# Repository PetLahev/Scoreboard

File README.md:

# Scoreboard 
Scoreboard created with [LED strips](https://www.amazon.com/FAVOLCANO-Waterproof-Feet%EF%BC%885M%EF%BC%89-Flexible-Lighting/dp/B012FFZP70/ref=sr_1_28_sspa?keywords=LED+Strips+red&qid=1554275786&s=gateway&sr=8-28-spons&psc=1), ~~[Arduino Nano](https://www.amazon.com/Arduino-A000005-ARDUINO-Nano/dp/B0097AU5OU/ref=sr_1_15?keywords=Arduino+Nano&qid=1554232867&s=gateway&sr=8-15)~~ [Arduino Uno](https://www.amazon.com/Arduino-A000066-ARDUINO-UNO-R3/dp/B008GRTSV6/ref=sr_1_3?keywords=arduino+UNO&qid=1555441457&s=gateway&sr=8-3) and some manual work. Handy for volleyball, table tennis, badminton, football etc.

### Why Arduino UNO
I wanted to use Nano and I designed the motherboard for using Nano but unfortunately it appeared to have one, not that serious problem for others,  but [blocker for me](https://stackoverflow.com/questions/55680065/arduino-nano-hm-10-module-not-receiving-data-on-mobile?noredirect=1#comment98070429_55680065). I was basically not able to send messages back to the HM-10 bluetooth module which is the 'main feature' of this whole scoreboard.
Thus after I built everything and was in the testing phase I found out that bluetooth communication is not working as I like. So instead of using the motherboard PCB I simply bought [UNO holder](https://store.arduino.cc/holder-type-uno) and a [terminal for UNO](https://www.amazon.com/Aideepen-Assembled-Prototype-Expansion-Bareboard/dp/B01JFQQXRS/ref=sr_1_3?keywords=arduino+UNO+terminal&qid=1555441354&s=gateway&sr=8-3) and made the scoreboard with it. Not that big problem as I have enough space in the box but hey ...

* 50 x 70 cm (19.7 x 27.55 inch) height x width
* Each segment 10 cm (3.93 inch) length so 20 cm (7.9 inch) one number! (*for points*)
* Each LED strip controlled by its own transistor
* Controlled by bluetooth module ([HM-10 Bluetooth 4.0 BLE](https://www.amazon.com/DSD-TECH-Bluetooth-iBeacon-Arduino/dp/B06WGZB2N4/ref=sr_1_1_sspa?keywords=HM-10-Bluetooth&qid=1554232302&s=gateway&sr=8-1-spons&psc=1))
    * Also possible to control via 433MHz module or an infra red (IR) controller
* You can use pre-defined setup for a game
* You can setup your own game
* Supports tiebreaks, sets and displaying players on service
* Score can be updated by buttons (either wired or wireless)
* As of April 2019 a free Androind application is used for controlling the scoreboard - [Serial Bluetooth Terminal](https://play.google.com/store/apps/details?id=de.kai_morich.serial_bluetooth_terminal&hl=en_US) v1.17
	* Update Feb 2021 - It was proven that the most convinient way how to control the scoreboard is an IR controller (people tend to prefer this way over others)
* Eagle schematic and boards included
* The scoreboard case designed on thinkercad.com
    * [The box](https://www.tinkercad.com/things/gNmK0jQ22qv)
    * [The display board](https://www.tinkercad.com/things/9Don7XhJEvx) - just for measuring purpose

## Setting the Serial Bluetooth Terminal
Just one device can be connected to the module at time!
Make sure you pair the bluetooth module with your smart phone, add it under the `Devices` tab and then go to the `Settings - Send` and set the `Newline` option to **none**. On the main menu tap on the connect symbol. You should get a text saying "Connected to unnamed". (*Make sure you bluetooth module is powered and the indication LED is blinking*)

## Settings
By default, the scoreboard is set as a clock (sets segment are used for seconds). There is no specific setting for turning the clock
off as this is always done by providing any setting. If you need to go back to the 'clock' mode, just turn the power off and then on.
You can setup your own game either in code - [globals.cpp](/Arduino/Scoreboard/src/globals.cpp) - or at runtime when sending the SETTING character via the Serial Bluetooth Terminal. The SETTING character is = `!` (*exclamation mark*). This behaves as a toggle switch so when send first time `!` the scoreboard will switch to 'setting mode' and will accept certain settings, when sending second time `!` it will end the 'setting mode' and will be ready for a game!

You can setup
* Number of sets (up to 9)
* Sets support - enabled/disabled
    * Number of points per a set (up to 99)
* Points difference to win a set
* Tiebreak support - enabled/disabled
    * Points in tiebreak
    * Points difference to win a tiebreak set
    * The tiebreak set
        * Set a number that represents the set in the match considered as tiebreak set. *For example, in tennis you would set number `7` here*
* Display player on service (*pre-set 4 players*) - enabled/disabled

### Application settings
The code now (*April 2019*) understands certain `key=value` pairs. Listed below but always check [settingController](/Arduino/Scoreboard/src/settingController.h) header file for the latest settings
* Enable displaying sets = `b`
* Sets per match = `s`
* Points per set = `e`
* Points difference to win a set = `d`
* Support tiebreak = `t`
* Set the tiebreak set = `q`
* Points in tiebreak = `f`
* Points difference to win a tiebreak = `w`
* Enable displaying a player on service = `r`
* Swap score = `$`
* Set player on service = `p` and then number 1 - 4
* Reset the whole game = `@`
* Turn sets segments to minute timer = `u`
    * Will automatically enable displaying sets

Examples of key-value setting

    b=true
    WIll enable sets (the LEDs will be powered)

    s=2
    A team/player needs to win 2 sets to win the match

    e=11
    A team/player needs to win 11 points to win a set
    (The points difference setting will be considered here)

    d=2
    A set will be considered as finished when the score between the teams/players
    1, reach the minimum points to win a set (e.g. 11)
    AND
    2, the difference is equal to 2
    examples: 11:9 or 13:11 or 12:10 or 21:19 etc.

    t=true
    Tiebreak is enabled

    q=2
    The tiebreak set is the second set to win. In other words this will be the third set
    For the above example the tiebreak settings will be considered when sets are 1:1

    f=9
    A team/player needs to win 9 points to win the tiebreak set

    w=2
    The tiebreak will be considered as finished when the score between the teams/players
    1, reach the minimum points to win the tiebreak set (e.g. 9)
    AND
    2, the difference is equal to 2
    examples: 9:7 or 10:8 or 11:9 etc.

    r=true
    Will enable displaying player on service (The LEDs will be powered)
    Note: There are always 4 players pre-set, not configurable as of April 2019)

    u=true
    Will turn the sets segments to display minute timer. So it will count from 0 to 9999 minutes

### Example of game settings
#### A free match (like football)
    b=false   ' disable sets
    s=0       ' no sets per match  
    e=99      ' set maximum of points
    t=false   ' tiebreak disabled
    r=false   ' disable displaying player on service

#### A beach volleyball match
    b=true    ' enable sets
    s=2       ' a team needs to win 2 sets to win a match
    e=21      ' a team needs to win 21 points to win a set
    d=2       ' the points difference between the two teams must be 2 to win a set
    t=reuw    ' tiebreak enabled
    q=2       ' the tiebreak set is the second one to win. So the sets score is 1:1
    f=15      ' a team needs to win 15 points to win the tiebreak set
    w=2       ' the points difference between the two teams must be 2 to win the tiebreak set
    r=true    ' enable displaying a player who serves

## How to use
Once your game is set and you leave the settings mode (*by sending `!` flag*) your match can start. Based on the type of your match the scoreboard will control all the aspect of the match you will just increase or decrease number of points for the **Home** or **Away** team

Send  
`h` - to give a point to **Home** team  
`a` - to give a point to **Away** team

If you make a mistake (*we all do*) you can take a point back.  
Send  
`v` - to decrease points of **Home** team  
`m` - to decrease score of **Away** team

**Please note:** Taking point back may have an affect on number of sets played, match finished, player on service etc. The code as of April 2019 cares just about simple cases and supports returning all back just for *one* point so if you made a mistake and give a point in the middle of set to a wrong team, taking the point back will work but if you made the same mistake when the team you gave won a set/match then taking the point back will NOT have any affect. It's better to start a new match by resetting the match and setting the correct score by sending few `h` or `a`.

## How to build
OK if you get here you actually may want to build your own scoreboard and I do understand that, it's much more fun!

If you just want to take the code and change it be aware that I didn't use the official Arduino IDE as I didn't find it as good as it should be. This project is made by [Visual Studio Code](https://code.visualstudio.com/) and [Platform IO](https://platformio.org/) extension both free. Once installed you should be able to build the project as it has all the settings done so you will get the right versions of used libraries and everything else. Please check [platformio.ini](/Arduino/platformio.ini) file to see if I added your Arduino board to the environment configuration. As of April 2019 I have this configuration

    [platformio]
    env_default = uno

    [env:nanoatmega328]
    platform = atmelavr
    board = nanoatmega328
    framework = arduino

    [env:uno]
    platform = atmelavr
    framework = arduino
    board = uno

The `env_default = uno` specifies for which board Platform IO builds the code, in this case is Arduino Uno. Make sure you have the right one here otherwise the code won't work.  
Let me also make you aware that I'm not C++ guy and I found it pretty hard to learn so the code is probably all messy but working.

If you also want to build the scoreboard case check the [Tinkercad page](https://www.tinkercad.com/things/gNmK0jQ22qv). I tried to make it in 1:5 scale but again it was my first experience with 3D software. The [shield](https://www.tinkercad.com/things/9Don7XhJEvx) is there only for measurement purpose. I just wanted to see to what size all the LED strips will fit and how it will look like. Based on the size I designed the [case](https://www.tinkercad.com/things/gNmK0jQ22qv).  
In terms of material use whatever will fit you. My original plan was using plastic because I didn't want to make it heavy but still not too fragile. For the first version I ended up with a 5mm wood board you can buy in hobby markets asked a joiner to cut the board into pieces and let him actually figure out how to put it all together, it cost me just ~$10 then you just need to a drill and couple screws and put it all together

To be continued

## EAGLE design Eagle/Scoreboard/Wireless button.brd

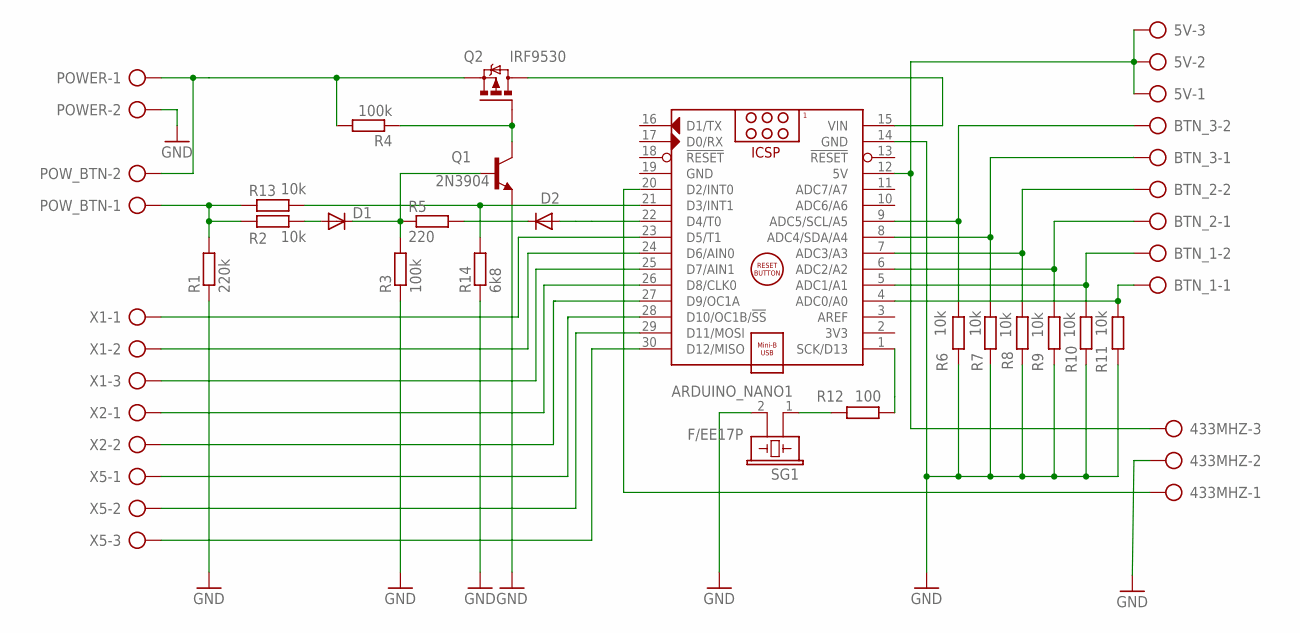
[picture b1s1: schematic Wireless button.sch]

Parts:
5V, 433MHZ: AK500/3
ARDUINO_NANO1: ARDUINO_NANO
BTN_1, BTN_2, BTN_3: AK500/2
D1, D2: 1N4148DO35-7; DO35-7
POWER: AK500/2
POW_BTN: AK500/2
Q1: 2N3904; TO92
Q2: IRF9530; TO220BV
R1: 220k; 0207/7
R2, R6, R7, R8, R9, R10, R11, R13: 10k; 0207/7
R3, R4: 100k; 0207/7
R5: 220; 0207/7
R12: 100; 0207/7
R14: 6k8; 0207/7
SG1: F/EE17P
X1, X5: AK500/3
X2: AK500/2

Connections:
5V: 5V.1, 5V.2, 5V.3, 433MHZ.3, ARDUINO_NANO1.12 (5V)
AWAY_DOWN: ARDUINO_NANO1.5 (ADC1/A1), BTN_1.2, R10.2
AWAY_UP: ARDUINO_NANO1.4 (ADC0/A0), BTN_1.1, R11.2
BUZZ: ARDUINO_NANO1.1 (SCK/D13), R12.2
GND: 433MHZ.2, ARDUINO_NANO1.14 (GND), ARDUINO_NANO1.19 (GND), POWER.2, Q1.3 (E), R1.1, R3.1, R6.1, R7.1, R8.1, R9.1, R10.1, R11.1, R14.1, SG1.2
HOME_DOWN: ARDUINO_NANO1.7 (ADC3/A3), BTN_2.2, R8.2
HOME_UP: ARDUINO_NANO1.6 (ADC2/A2), BTN_2.1, R9.2
unnamed: ARDUINO_NANO1.22 (D4/T0), D2.A
unnamed: Q1.1 (C), Q2.G, R4.1
unnamed: ARDUINO_NANO1.23 (D5/T1), X1.1
unnamed: D1.A, R2.2
unnamed: D1.C, Q1.2 (B), R3.2, R5.1
unnamed: D2.C, R5.2
unnamed: ARDUINO_NANO1.24 (D6/AIN0), X1.2
unnamed: ARDUINO_NANO1.25 (D7/AIN1), X1.3
unnamed: R12.1, SG1.1
unnamed: 433MHZ.1, ARDUINO_NANO1.20 (D2/INT0)
unnamed: ARDUINO_NANO1.26 (D8/CLK0), X2.1
unnamed: ARDUINO_NANO1.27 (D9/OC1A), X2.2
unnamed: ARDUINO_NANO1.28 (D10/OC1B/!SS), X5.1
unnamed: ARDUINO_NANO1.29 (D11/MOSI), X5.2
unnamed: ARDUINO_NANO1.30 (D12/MISO), X5.3
unnamed: ARDUINO_NANO1.21 (D3/INT1), R13.2, R14.2
OFF: POW_BTN.1, R1.2, R2.1, R13.1
POWER: POWER.1, POW_BTN.2, Q2.S, R4.2
RESET: ARDUINO_NANO1.9 (ADC5/SCL/A5), BTN_3.2, R6.2
SWAP: ARDUINO_NANO1.8 (ADC4/SDA/A4), BTN_3.1, R7.2
VCC: ARDUINO_NANO1.15 (VIN), Q2.D

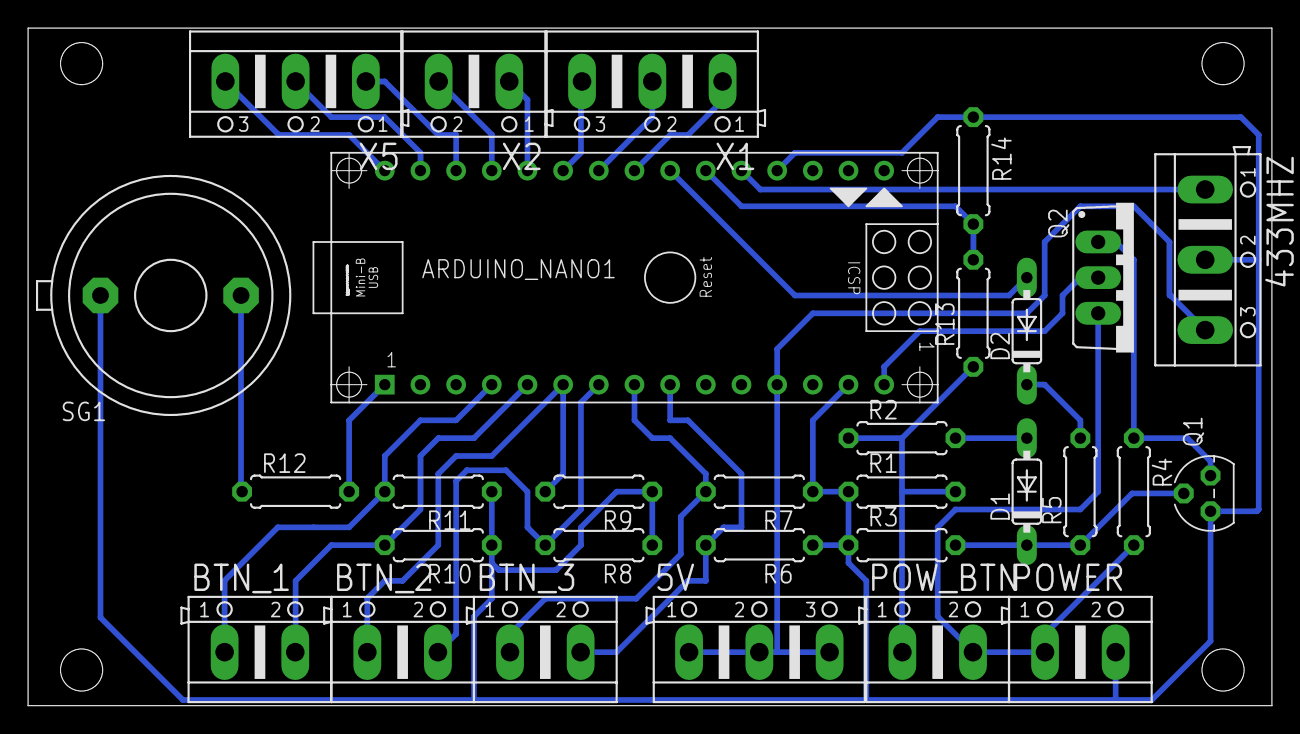
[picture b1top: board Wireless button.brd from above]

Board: 2 copper layers, 88.6 x 48.2 mm, 30 parts (0 on the bottom side), 28 nets.

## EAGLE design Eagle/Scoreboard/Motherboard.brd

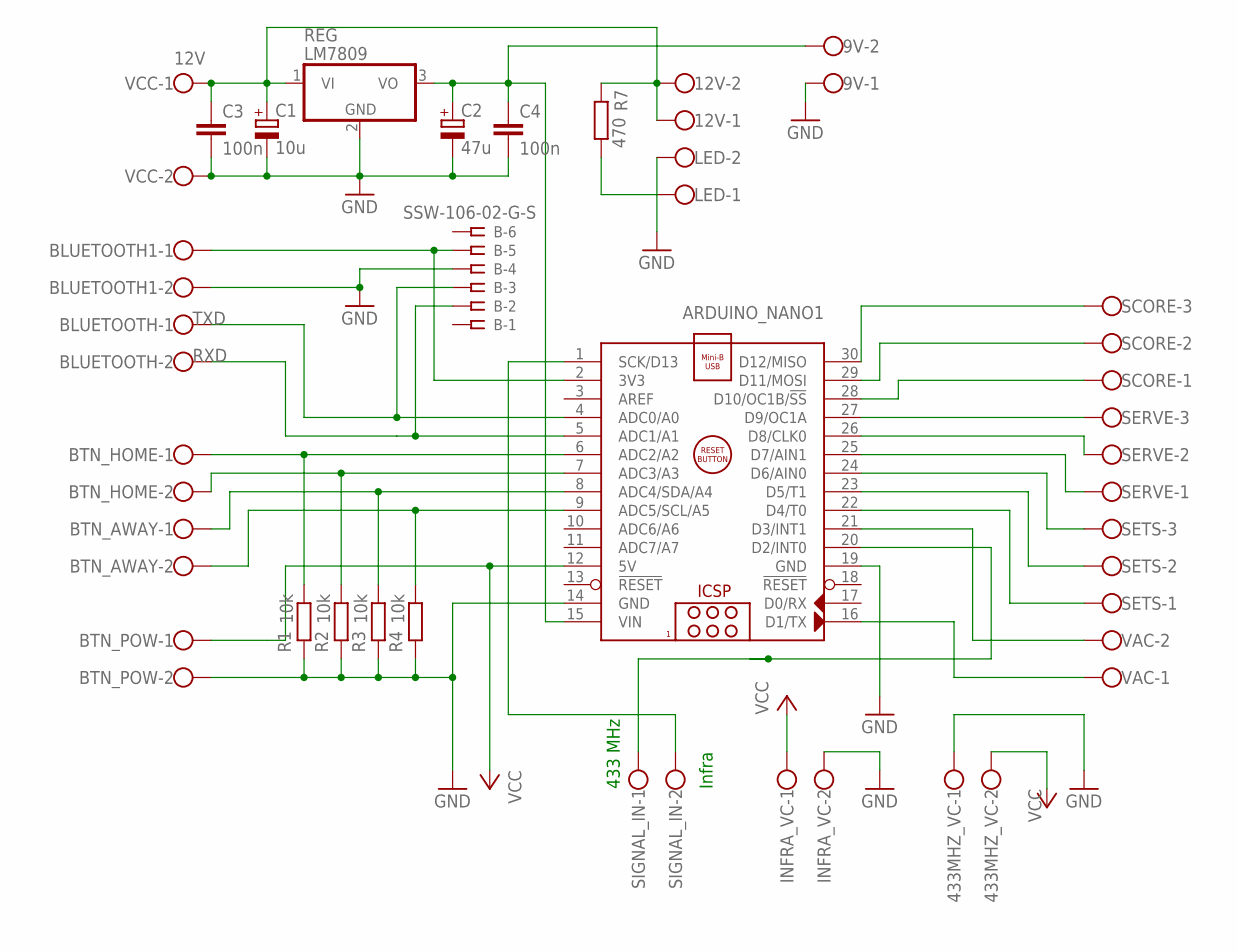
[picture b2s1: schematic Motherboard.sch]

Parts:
9V, 12V, 433MHZ_VC: W237-102
ARDUINO_NANO1: ARDUINO_NANO
B: SSW-106-02-G-S
BLUETOOTH, BLUETOOTH1: W237-102
BTN_AWAY: W237-102
BTN_HOME: W237-102
BTN_POW: W237-102
C1: 10u; E2-4
C2: 47u; E2-4
C3, C4: 100n; C5B2.5
INFRA_VC: W237-102
LED: W237-102
R1, R2, R3, R4: 10k; 0204/7
R7: 470; 0204/7
REG: LM7809; TO220H
SCORE: W237-103
SERVE: W237-103
SETS: W237-103
SIGNAL_IN: W237-102
VAC: W237-102
VCC: W237-102

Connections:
3V3: ARDUINO_NANO1.2 (3V3), B.5, BLUETOOTH1.1
12V: 12V.1, 12V.2, C1.+, C3.1, R7.2, REG.1 (VI), VCC.1
433MHZ: ARDUINO_NANO1.20 (D2/INT0), SIGNAL_IN.1
A2: ARDUINO_NANO1.6 (ADC2/A2), BTN_HOME.1, R1.1
A3: ARDUINO_NANO1.7 (ADC3/A3), BTN_HOME.2, R2.1
A4: ARDUINO_NANO1.8 (ADC4/SDA/A4), BTN_AWAY.1, R3.1
A5: ARDUINO_NANO1.9 (ADC5/SCL/A5), BTN_AWAY.2, R4.1
GND: 9V.1, 433MHZ_VC.1, ARDUINO_NANO1.14 (GND), ARDUINO_NANO1.19 (GND), B.4, BLUETOOTH1.2, BTN_POW.2, C1.-, C2.-, C3.2, C4.2, INFRA_VC.2, LED.2, R1.2, R2.2, R3.2, R4.2, REG.2 (GND), VCC.2
INFRA: ARDUINO_NANO1.1 (SCK/D13), SIGNAL_IN.2
unnamed: ARDUINO_NANO1.21 (D3/INT1), VAC.2
unnamed: ARDUINO_NANO1.16 (D1/TX), VAC.1
unnamed: LED.1, R7.1
RXD: ARDUINO_NANO1.5 (ADC1/A1), B.2, BLUETOOTH.2
SCORE_1: ARDUINO_NANO1.28 (D10/OC1B/!SS), SCORE.1
SCORE_2: ARDUINO_NANO1.29 (D11/MOSI), SCORE.2
SCORE_3: ARDUINO_NANO1.30 (D12/MISO), SCORE.3
SERVE_1: ARDUINO_NANO1.25 (D7/AIN1), SERVE.1
SERVE_2: ARDUINO_NANO1.26 (D8/CLK0), SERVE.2
SERVE_3: ARDUINO_NANO1.27 (D9/OC1A), SERVE.3
SETS_1: ARDUINO_NANO1.22 (D4/T0), SETS.1
SETS_2: ARDUINO_NANO1.23 (D5/T1), SETS.2
SETS_3: ARDUINO_NANO1.24 (D6/AIN0), SETS.3
TXD: ARDUINO_NANO1.4 (ADC0/A0), B.3, BLUETOOTH.1
VCC: 433MHZ_VC.2, ARDUINO_NANO1.12 (5V), BTN_POW.1, INFRA_VC.1
VIN_9V: 9V.2, ARDUINO_NANO1.15 (VIN), C2.+, C4.1, REG.3 (VO)

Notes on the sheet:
RXD
TXD
433 MHz
Infra

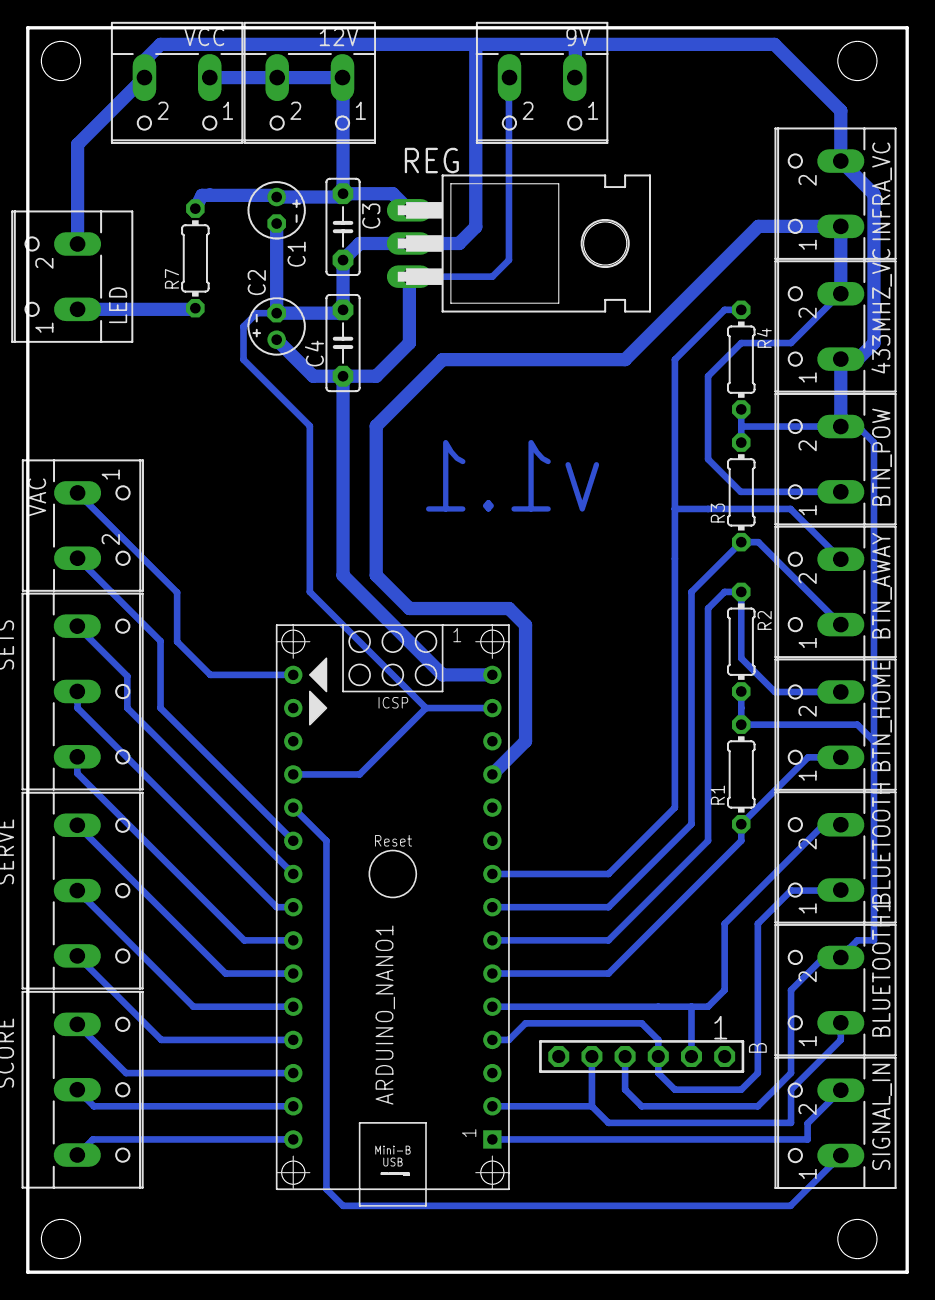
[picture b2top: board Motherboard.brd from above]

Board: 2 copper layers, 67.3 x 95.2 mm, 28 parts (0 on the bottom side), 25 nets.

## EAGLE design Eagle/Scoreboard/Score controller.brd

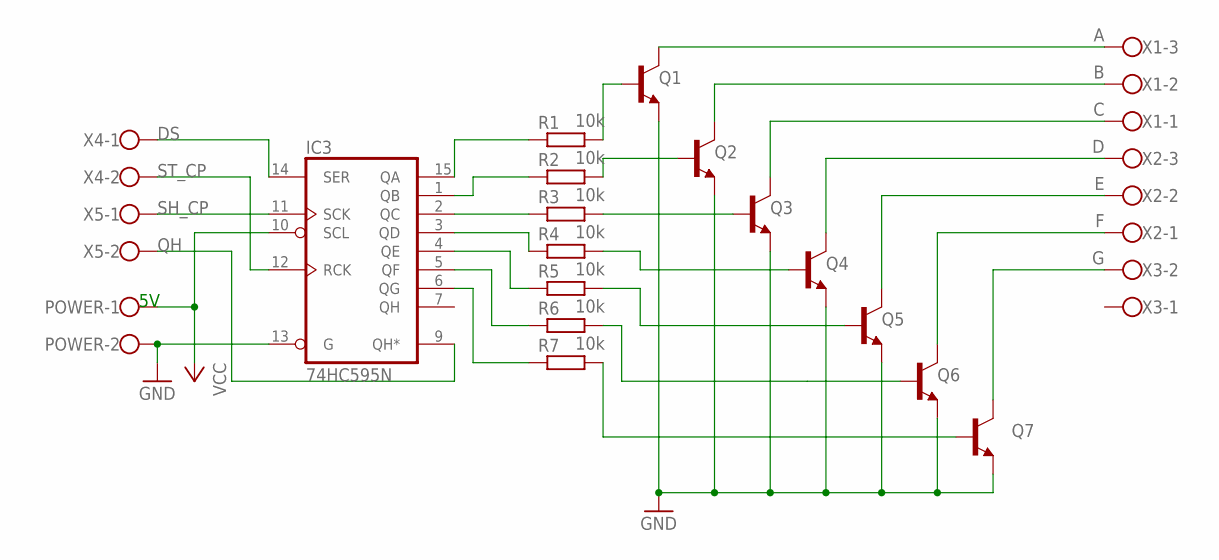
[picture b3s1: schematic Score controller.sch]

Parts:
IC3: 74HC595N; DIL16
POWER: W237-102
Q1, Q2, Q3, Q4, Q5, Q6, Q7: BC338-40; TO92-EBC
R1, R2, R3, R4, R5, R6, R7: 10k; 0204/7
X1, X2: W237-103
X3, X4, X5: W237-102

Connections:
A: Q1.C, X1.3
B: Q2.C, X1.2
C: Q3.C, X1.1
D: Q4.C, X2.3
DS: IC3.14 (SER), X4.1
E: Q5.C, X2.2
F: Q6.C, X2.1
G: Q7.C, X3.2
GND: IC3.8 (GND), IC3.13 (G), POWER.2, Q1.E, Q2.E, Q3.E, Q4.E, Q5.E, Q6.E, Q7.E
unnamed: IC3.1 (QB), R2.1
unnamed: Q1.B, R1.2
unnamed: IC3.2 (QC), R3.1
unnamed: IC3.15 (QA), R1.1
unnamed: Q2.B, R2.2
unnamed: IC3.3 (QD), R4.1
unnamed: IC3.4 (QE), R5.1
unnamed: IC3.5 (QF), R6.1
unnamed: IC3.6 (QG), R7.1
unnamed: Q3.B, R3.2
unnamed: Q4.B, R4.2
unnamed: Q5.B, R5.2
unnamed: Q6.B, R6.2
unnamed: Q7.B, R7.2
QH: IC3.9 (QH*), X5.2
SH_CP: IC3.11 (SCK), X5.1
ST_CP: IC3.12 (RCK), X4.2
VCC: IC3.10 (SCL), IC3.16 (VCC), POWER.1

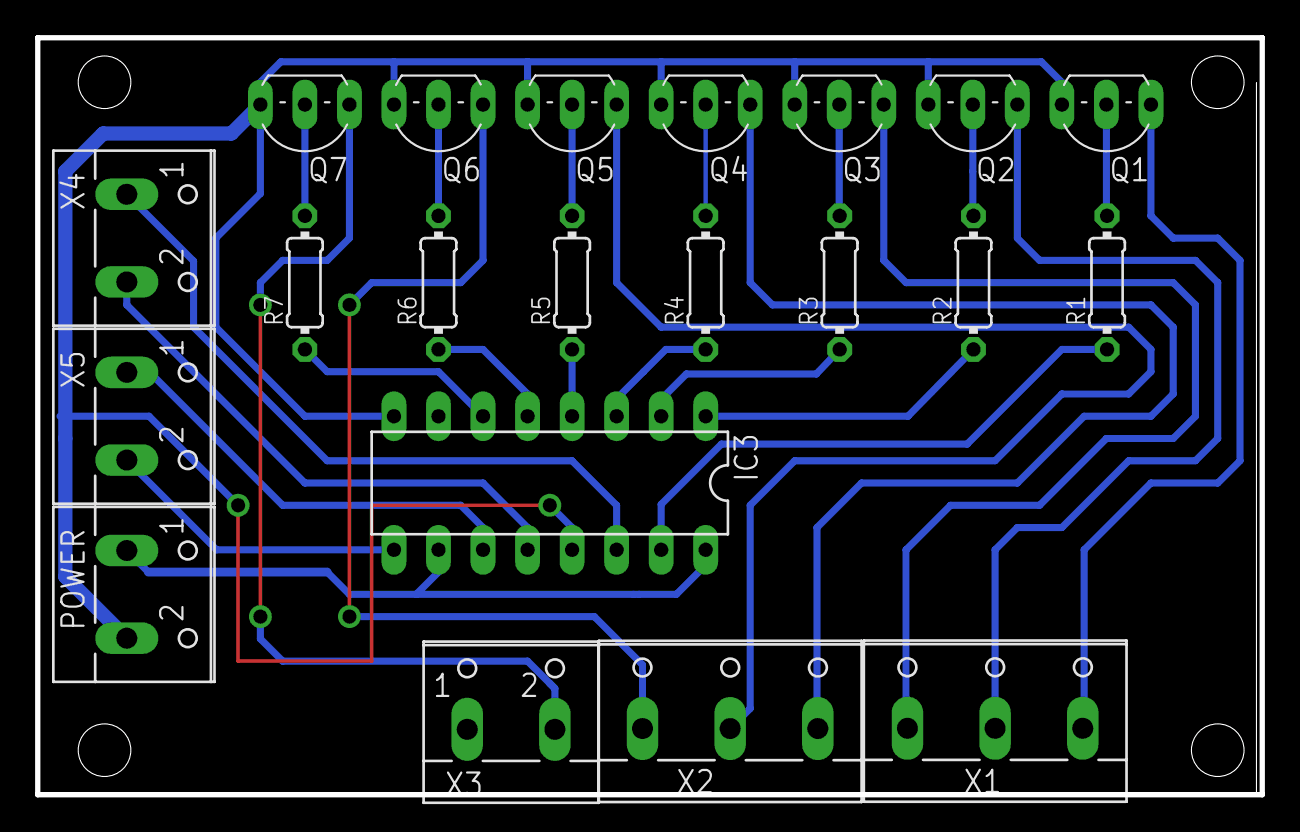
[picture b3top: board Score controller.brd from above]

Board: 2 copper layers, 69.8 x 43.2 mm, 21 parts (0 on the bottom side), 27 nets.

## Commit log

2018-09-01 Adding motherboard scheme
2018-09-01 Added other conectors for devices
2018-09-01 Added mising resistor, better PCB positioning
2018-09-08 Added schematic and board for score controller that controls the individual LED strip. There must one board for 7 LED strips max
2018-09-18 Changed transistor type for score controller, changed number of terminals to 8. Motherboard still TBD
2018-10-11 Added initial structure
2018-10-15 Continuing adding project structure
2018-10-18 Added logic for ending sets and match, started with logic for servers
2018-10-19 Added logic for player who serves
2018-10-19 Inital changes for display controller
2018-10-20 Added code for displaying score on scoreboard
2018-10-20 Added logic for displaying sets and player who should score
2018-10-20 Finished code for blinking display + code for reseting game. Need to provide some class for logging information that applications can read it
2018-10-20 Fixed build errors
2018-10-28 Added support for tiebreak
2019-03-11 Added setting controller class with simple imeplemntation of reading the current settings.
2019-03-12 Added more code for settingController. Still TBC
2019-03-13 Changed matherboard scheme and start designing PCB
    Scheme was changed to make easier PCB design. Still need to finish VCC layer on TOP layer
2019-03-16 Finalized board for motherboard
2019-03-16 Added capacitors for filtering
2019-03-29 Add second environment for testing board - ArduinoUno
2019-03-29 Ignoring VS code ipch folder
2019-03-29 Made changes after testing with Uno. Settings class should work
2019-03-29 Chnaged all switch transistor to BC-337 TO92 AMMO
2019-03-29 All pins were confirmed, PCB designed
2019-03-29 Fixed code for score controller
2019-03-31 Added more logging fixed bug with displaying numbers above 9
2019-03-31 Added pin mode, not really sure I had to do that
2019-03-31 Finished code for settings
2019-03-31 for ARDUINO NANO I need to switch the pins for bluetooth module!!
2019-03-31 Added polygons
2019-03-31 Added polygon and make more space for screws
2019-03-31 Changed the board to be just one layer
2019-04-01 Added scheme for wiring
2019-04-01 Updated pins to reflect PCB
2019-04-02 Added new readme and some images
2019-04-02 Added new headings
2019-04-02 Uploaded smaller image of powered scoreboard
2019-04-02 Added smaller images and adjusted readme
2019-04-02 link to image
2019-04-02 Updated image llinks
2019-04-02 Fixed errors
2019-04-03 Added link to LED strips and added size of the board
2019-04-03 Added images of PCB to the readme
2019-04-03 Added more space for screws
2019-04-03 Made the pictures of PCB smaller
2019-04-03 Added How to build section
2019-04-16 Added connector labels for printing
2019-04-16 Added fixes during real testing
2019-04-16 Ammended wiki to reflect latest changes
2019-04-16 Fixed error with A6, A7 pin plus couple major changes
    The pin A6 & A7 cannot be used for anything digital on Nano. So removed
    Also moved the bluetooth pins and removed buttons for sets to get some free pin. Made the bluetooth module powered by 3.3V so we don't need to use voltage divider. Also made the 9V available so we ca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
2019-04-23 Changed pins to reflect changes for UNO
2019-04-23 Added labels for UNO terminal
2019-04-26 Finished code for setting players, added reset command , minor changes
2019-04-26 Added new commands to wiki
2019-04-29 PCBs images and back side
2019-04-29 Re-color connectors
2019-04-29 Added new images
2019-04-30 Tryaing adding CI configuration file
2019-04-30 Minor update of the readme file
2019-04-30 Added build image
2019-04-30 Updated readme with build status
2019-04-30 Printing result of a set and match to bluetooth
2019-04-30 Moving travis to top folder
2019-04-30 Correct typo in the file name, updated travis
2019-04-30 Another attempt to make travis build work
2019-05-01 Re-colored connector labels
2019-05-01 Fixed connection plan, added pins
2019-05-01 Added Eagle schemes as PDFs
2019-05-01 Initial structure for the wireless controller
2019-05-01 added code for all buttons
2019-05-06 Added config file plus minor changes for LED
2019-05-28 CHanged pins and removed unused buttons
2019-05-30 Added scheme for wireless buttons with self shutdown
2019-06-05 Added code for self shutdown and power button. Pins need to be verified
2019-06-05 Adjusted code for wireless communication
2019-06-13 Minor changes for tones. Pins are not aligned with the scheme
2019-06-13 Updated scheme and added board. Pins are not zet aligned with code
2019-06-28 Added paper cover on the box
2019-06-28 Synchronize pins with PCB
2019-06-28 Changed deprecated env var
2019-06-28 Platform IO supporting files
2019-06-28 Hash to ignore
2019-06-28 hash extension to ignore
2019-06-28 Cleaning platform IO stuff
2019-06-28 Increased inactivity period to 10 mins
2019-06-28 Power for 433Mhz transmitter taking from 5V
2019-06-28 433Mhz module done
2019-07-02 Added support for turning sets segments to minute counter
2019-07-03 added pio folder to ignore file
2019-07-03 Displaying minutes are not taken directly from millis. Added handling for long running games
2019-07-03 Added minute timer settings
2019-09-12 Fixed bug with settings mode. Added code for turning off sets and players
2020-02-10 Set up a free play as the default setting. Fixed bug with minutes
2020-03-06 Updated project settings as per official documentation and added new IR remote library
2020-03-06 Minor update for the IR remote control
2020-03-06 Added IR Remote lib to the travis config
2021-02-04 BREAKING CHANGE. Changed pin, you need to re-connect
2021-02-04 Added code for turning the scoreboard to clock mode
2021-02-04 Updated schema to reflect latest changes
    The 433Mhz pin was moved to A3 and pin A4 and A5 are now used by the real time clock generator
2021-02-04 Updated motherboard scheme to reflect latest changes
2021-02-05 reduced delay for clock mode, add IR method
2021-02-05 Updated wiring
2021-02-06 Added leading zero for clock mode
2021-02-06 Added new IR commands for new remote controler TBC
2021-02-06 If RTC not found, script will still continue
2021-02-06 Added pre-defined game settings
2021-02-07 Always turning off clock and minute mode for pre-defined settings
2021-02-07 Update wiring scheme to match real wirring with UNO
2021-02-07 Create Scoreboard wire connection.pdf
    Added wiring scheme
2021-02-07 Changed python to 3.6
2021-02-07 Added RTC library as dependency
2021-02-08 Fixed bug with leadin zeros, added reset after applying a setting
2021-02-08 Fixed bug for leading zero for minutes
